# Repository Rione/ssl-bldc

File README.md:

# Ri-one BLDC Driver V1

|  | IC |
| --- | --- |
| MOSFET | [SIZ254DT-T1-GE3](https://www.mouser.jp/ProductDetail/Vishay-Siliconix/SIZ254DT-T1-GE3?qs=pUKx8fyJudCKVjpWQE2G2A%3D%3D) |
| MCU | [STM32F446RET6](https://jp.rs-online.com/web/p/microcontrollers/1106621) |
| Gate Driver | [DVR8300DRGER](https://www.ti.com/product/DRV8300/part-details/DRV8300DRGER) |
| CAN Transceiver | [TJA1441AT](https://akizukidenshi.com/catalog/g/gI-17464/) |
| Shunt Resistor| 10mΩ | 
| 3.3V Regulator | [AP7333-33SAG](https://akizukidenshi.com/catalog/g/gI-11360/) |
| Motor | [EC 45 flat 30W](https://www.maxongroup.com/medias/sys_master/root/8846629470238/20-JP-285.pdf)|

---

初めて作ったモータドライバ基板です．
記事も書いたので，良かったら見てください．
[tomixrm 初のモタドラ設計！！ゲート抵抗を計算して求めてみた](https://tomixrm.vercel.app/2e7cb67096e143f2a43334a63c00d47e)

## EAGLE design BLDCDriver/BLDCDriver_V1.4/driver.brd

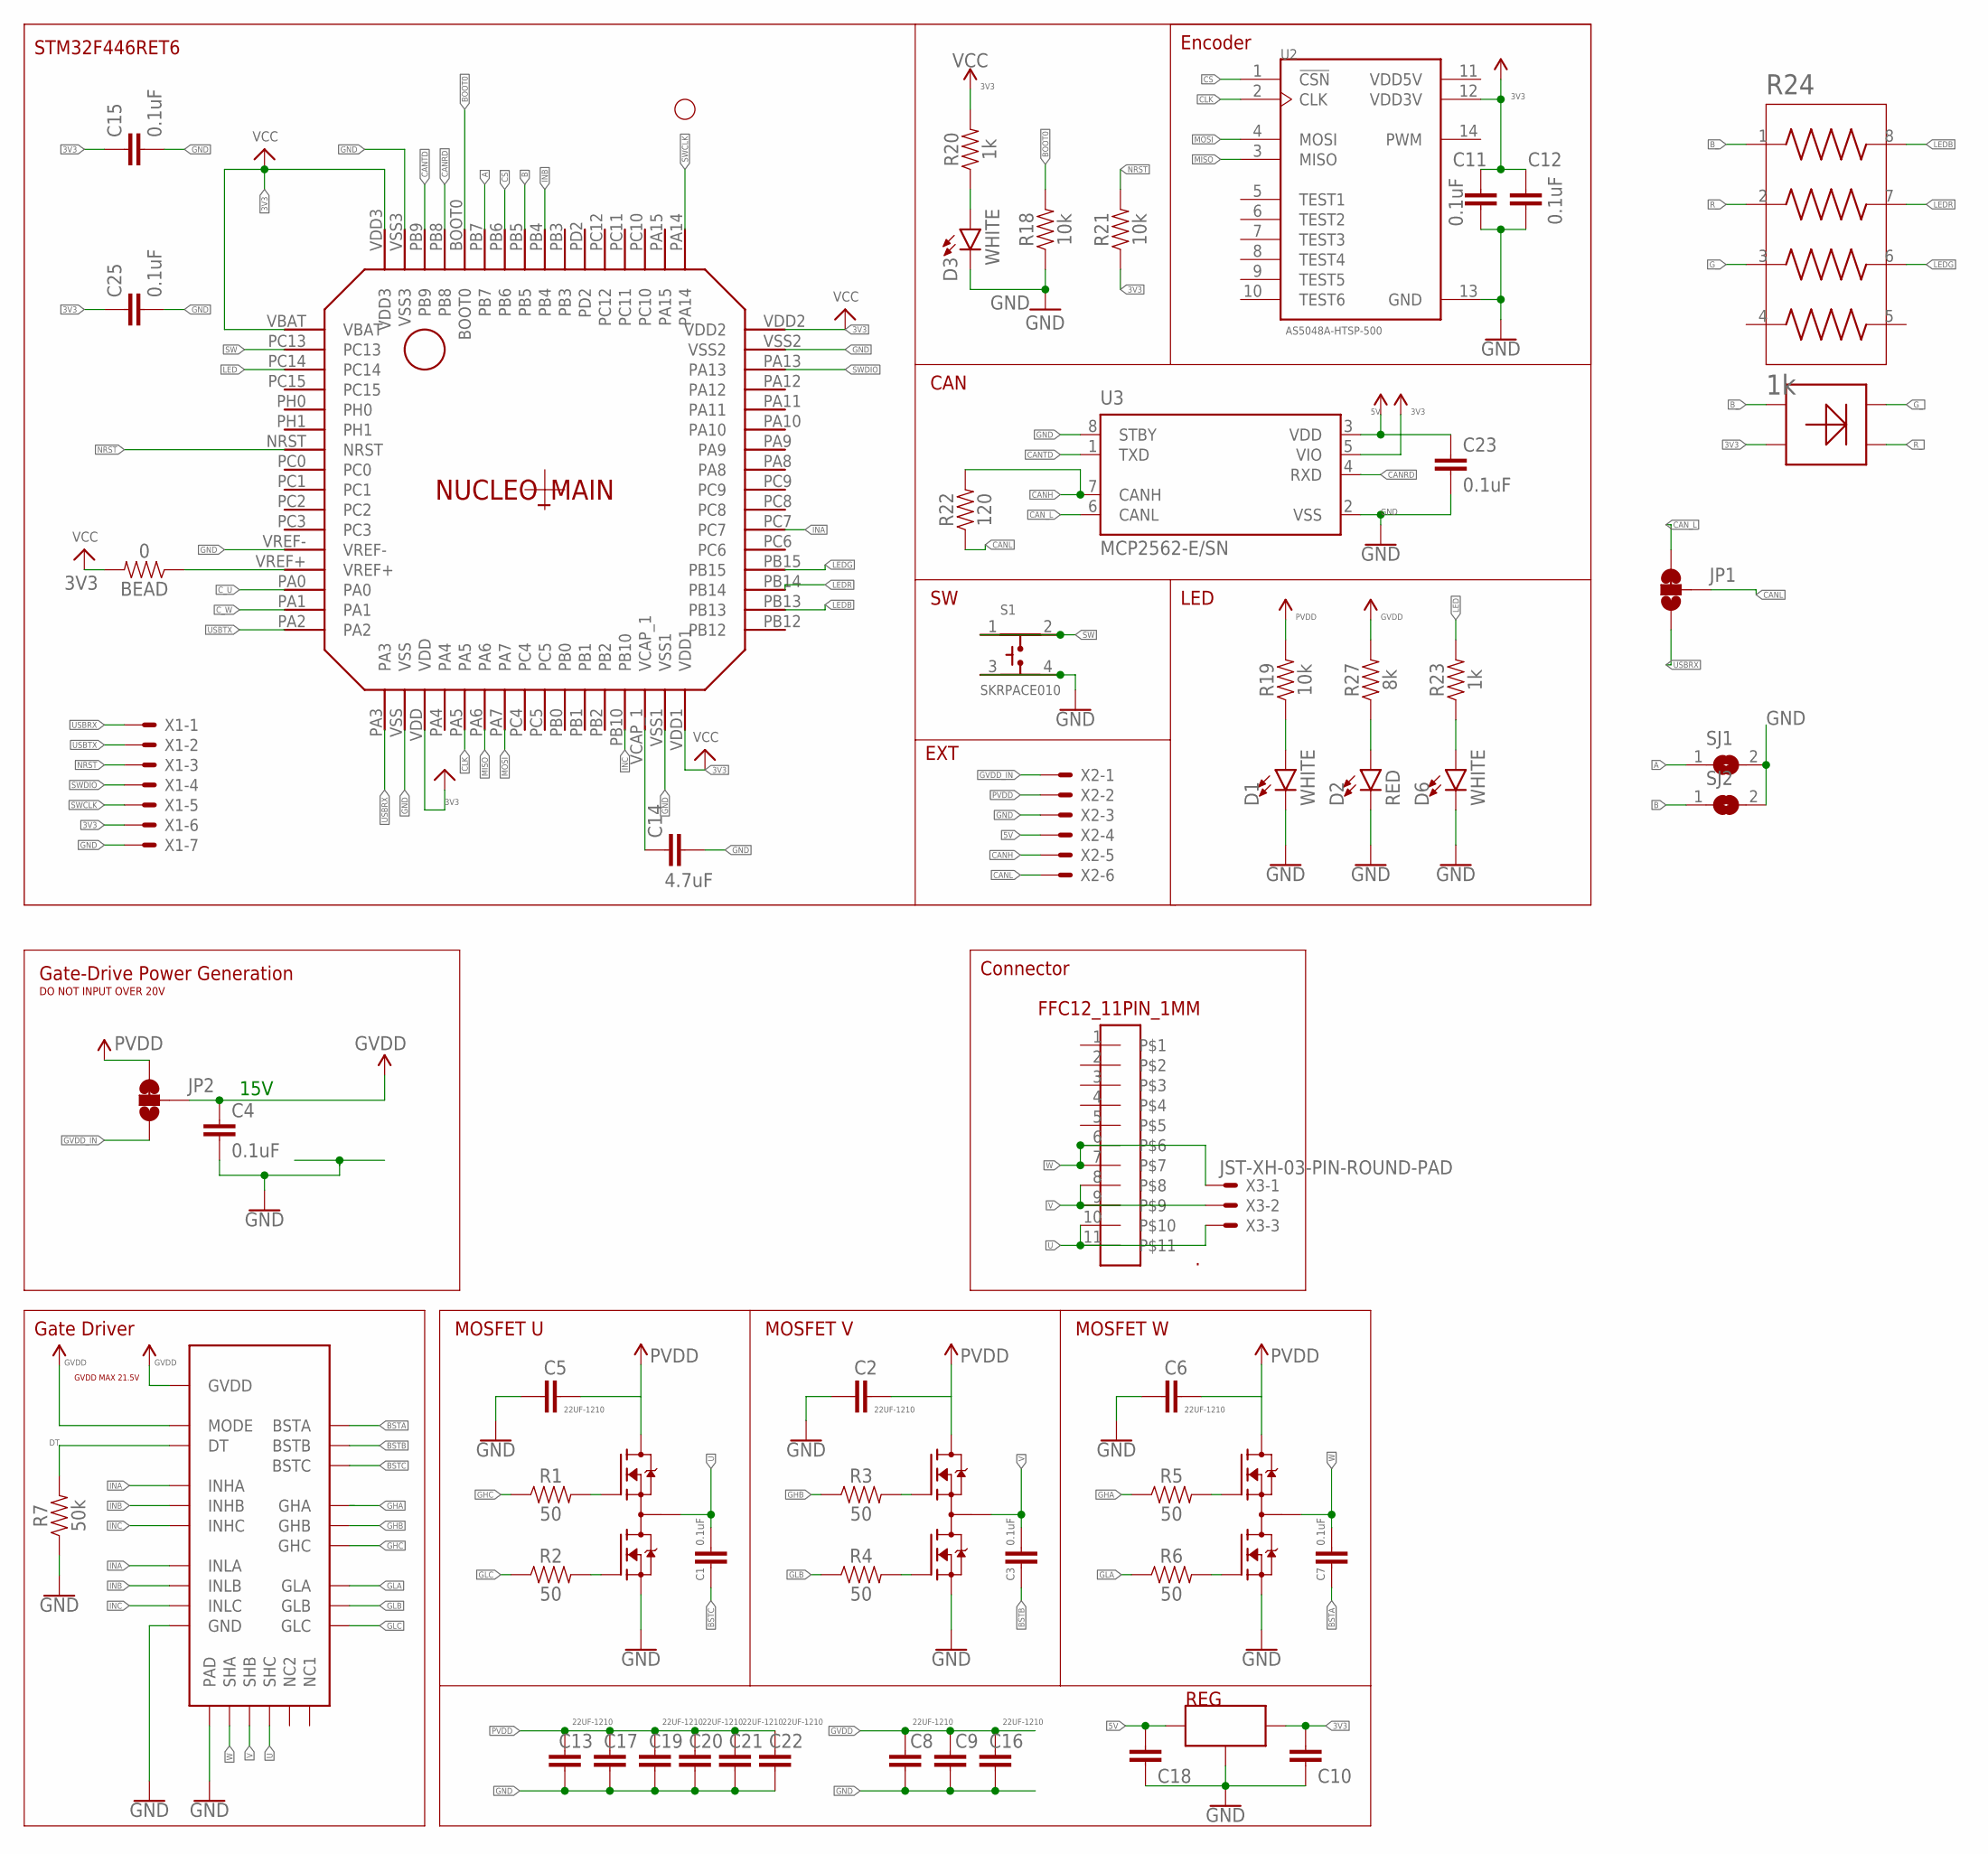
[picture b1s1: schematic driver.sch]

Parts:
.: FFC12_11PIN_1MM; CON-SMT-FFCFPC_52207-1185
BEAD: 0; 0603
C1, C3, C4, C7, C11, C12, C15, C23, C25: 0.1uF; 0603
C2, C5, C6, C8, C9, C13, C16, C17, C19, C20, C21, C22: 22UF-1210; 1210
C10, C18: 0.1UF; 1608
C14: 4.7uF; 0603
D1, D3, D6: WHITE; LED-0603
D2: RED; LED-0603
JP1, JP2: JUMPER-SMT_3_1-NC_TRACE_SILK; SMT-JUMPER_3_1-NC_TRACE_SILK
NUCLEO_MAIN: F446RET6; STM32F446RET6
Q2, Q3, Q4: SIZ240DT-T1-GE3; TRANS_SIZ240DT-T1-GE3
R1, R2, R3, R4, R5, R6: 50; 0603
R7: 50k; 0603
R18, R21: 10k; R0603
R19: 10k; 0603
R20: 1k; R0603
R22: 120; 0603
R23: 1k; 0603
R24: 1k; RESCAXS50P200X100X45-8N
R27: 8k; 0603
REG: AP7333; SOT95P237X112-3N
S1: SKRPACE010; SW_SKRPACE010
SJ1, SJ2: SJ
U1: QFN50P400X400X100-25NDRV8300DRGER; QFN50P400X400X100-25N
U2: AS5048A-HTSP-500; SOP65P640X120-14N
U3: MCP2562-E/SN; SOIC127P600X175-8N
U$1: LED; LED_AAA3528LSEKJ3ZGKQBKS
X1: JST-XH-07-PIN-ROUND-PAD; JST-XH-07-PACKAGE-ROUND-PAD
X2: JST-XH-06-PIN-LONG-PAD; JST-XH-06-PACKAGE-LONG-PAD
X3: JST-XH-03-PIN-ROUND-PAD; JST-XH-03-PACKAGE-ROUND-PAD

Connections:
3V3: BEAD.2, C10.1, C11.1, C12.1, C15.1, C25.1, NUCLEO_MAIN.VBAT, NUCLEO_MAIN.VDD, NUCLEO_MAIN.VDD1, NUCLEO_MAIN.VDD2, NUCLEO_MAIN.VDD3, R20.2, R21.1, REG.2 (OUT), U2.12 (VDD3V), U3.5 (VIO), U$1.4 (GND), X1.6
5V: C18.1, C23.1, REG.1 (IN), U3.3 (VDD), X2.4
A: NUCLEO_MAIN.PB7, SJ1.1
B: NUCLEO_MAIN.PB5, SJ2.1
BOOT0: NUCLEO_MAIN.BOOT0, R18.2
BSTA: C7.1, U1.BSTA
BSTB: C3.1, U1.BSTB
BSTC: C1.1, U1.BSTC
B_: R24.1, U$1.1 (B)
CANH: R22.2, U3.7 (CANH), X2.5
CANL: JP1.2, R22.1, X2.6
CANRD: NUCLEO_MAIN.PB8, U3.4 (RXD)
CANTD: NUCLEO_MAIN.PB9, U3.1 (TXD)
CAN_L: JP1.3, U3.6 (CANL)
CLK: NUCLEO_MAIN.PA5, U2.2 (CLK)
CS: NUCLEO_MAIN.PB6, U2.1 (!CSN)
C_U: NUCLEO_MAIN.PA0
C_W: NUCLEO_MAIN.PA1
DT: R7.2, U1.DT
GHA: R5.1, U1.GHA
GHB: R3.1, U1.GHB
GHC: R1.1, U1.GHC
GLA: R6.1, U1.GLA
GLB: R4.1, U1.GLB
GLC: R2.1, U1.GLC
GND: C2.1, C4.2, C5.1, C6.1, C8.1, C9.1, C10.2, C11.2, C12.2, C13.1, C14.2, C15.2, C16.1, C17.1, C18.2, C19.1, C20.1, C21.1, C22.1, C23.2, C25.2, D1.C, D2.C, D3.C, D6.C, NUCLEO_MAIN.VREF-, NUCLEO_MAIN.VSS, NUCLEO_MAIN.VSS1, NUCLEO_MAIN.VSS2, NUCLEO_MAIN.VSS3, Q2.5 (S2), Q2.6 (S2), Q2.7 (S2), Q3.5 (S2), Q3.6 (S2), Q3.7 (S2), Q4.5 (S2), Q4.6 (S2), Q4.7 (S2), R7.1, R18.1, REG.3 (GND), S1.3, S1.4, SJ1.2, SJ2.2, U1.GND, U1.PAD, U2.13 (GND), U3.2 (VSS), U3.8 (STBY), X1.7, X2.3
GVDD: C4.1, C8.2, C9.2, C16.2, JP2.2, R27.2, U1.GVDD, U1.MODE
GVDD_IN: JP2.1, X2.1
G_: R24.3, U$1.2 (G)
HA: Q4.1 (G1), R5.2
HB: Q3.1 (G1), R3.2
HC: Q2.1 (G1), R1.2
INA: NUCLEO_MAIN.PC7, U1.INHA, U1.INLA
INB: NUCLEO_MAIN.PB4, U1.INHB, U1.INLB
INC: NUCLEO_MAIN.PB10, U1.INHC, U1.INLC
L: D3.A, R20.1
LA: Q4.8 (G2), R6.2
LB: Q3.8 (G2), R4.2
LC: Q2.8 (G2), R2.2
LED: NUCLEO_MAIN.PC14, R23.2
LEDB: NUCLEO_MAIN.PB13, R24.8
LEDG: NUCLEO_MAIN.PB15, R24.6
LEDR: NUCLEO_MAIN.PB14, R24.7
MISO: NUCLEO_MAIN.PA6, U2.3 (MISO)
MOSI: NUCLEO_MAIN.PA7, U2.4 (MOSI)
unnamed: D1.A, R19.1
unnamed: D2.A, R27.1
unnamed: D6.A, R23.1
NRST: NUCLEO_MAIN.NRST, R21.2, X1.3
PVDD: C2.2, C5.2, C6.2, C13.2, C17.2, C19.2, C20.2, C21.2, C22.2, JP2.3, Q2.2 (D1), Q2.3 (D1), Q2.4 (D1), Q2.10 (D1), Q3.2 (D1), Q3.3 (D1), Q3.4 (D1), Q3.10 (D1), Q4.2 (D1), Q4.3 (D1), Q4.4 (D1), Q4.10 (D1), R19.2, X2.2
R_: R24.2, U$1.3 (R)
SW: NUCLEO_MAIN.PC13, S1.1, S1.2
SWCLK: NUCLEO_MAIN.PA14, X1.5
SWDIO: NUCLEO_MAIN.PA13, X1.4
U: ..10, ..11, C1.2, Q2.9 (S1/D2), U1.SHC, X3.3
USBRX: JP1.1, NUCLEO_MAIN.PA3, X1.1
USBTX: NUCLEO_MAIN.PA2, X1.2
V: ..8, ..9, C3.2, Q3.9 (S1/D2), U1.SHB, X3.2
VCAP: C14.1, NUCLEO_MAIN.VCAP_1
VDD5V: U2.11 (VDD5V)
VDDA: BEAD.1, NUCLEO_MAIN.VREF+
W: ..6, ..7, C7.2, Q4.9 (S1/D2), U1.SHA, X3.1

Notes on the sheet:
GVDD MAX 21.5V
15V
Gate-Drive Power Generation
Gate Driver
MOSFET U
Connector
Encoder
STM32F446RET6
MOSFET V
MOSFET W
DO NOT INPUT OVER 20V
CAN
LED
EXT

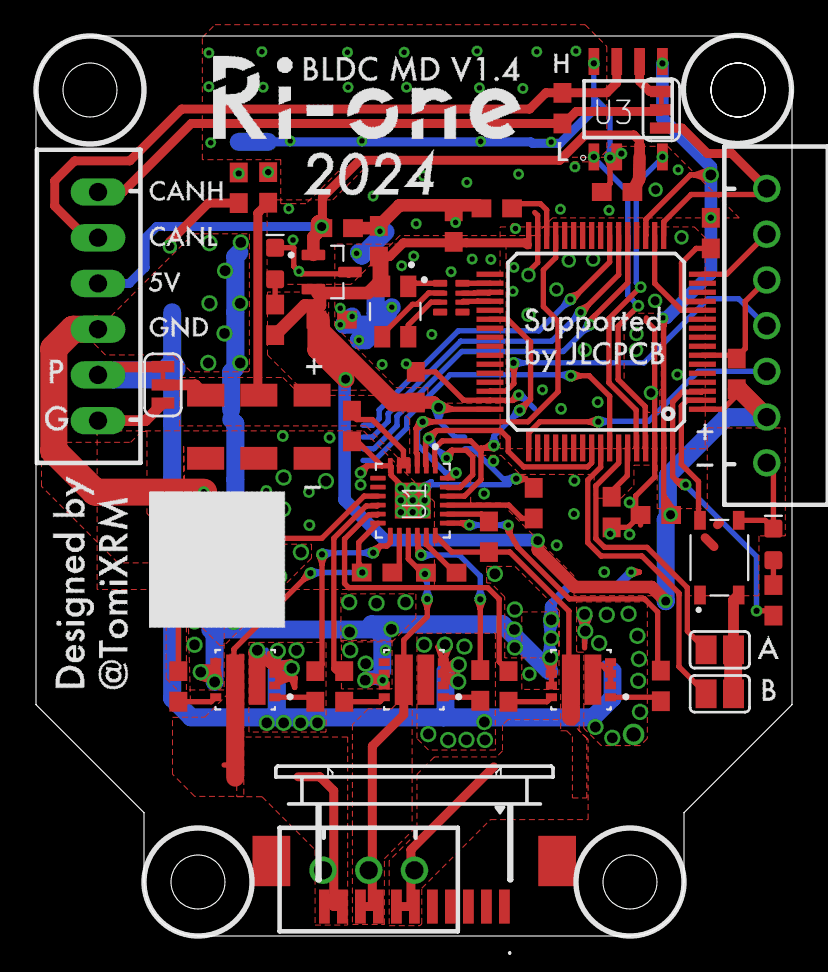
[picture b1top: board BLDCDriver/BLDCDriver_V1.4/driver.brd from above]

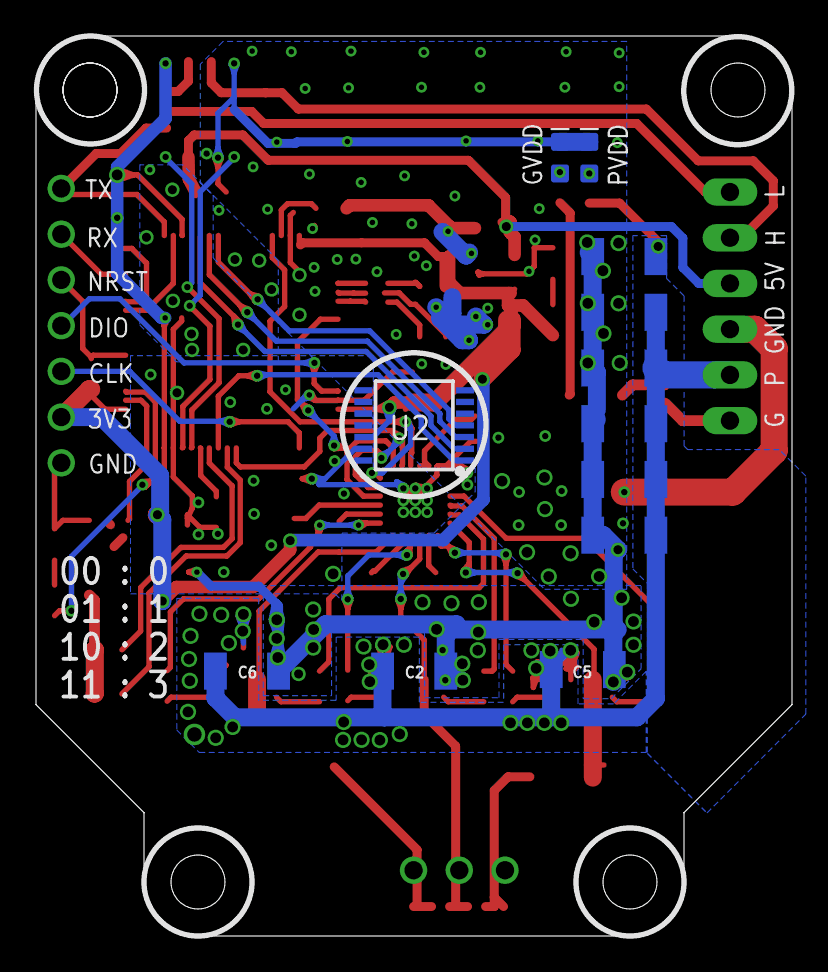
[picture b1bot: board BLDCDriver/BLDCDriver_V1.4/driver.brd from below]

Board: 2 copper layers, 42.0 x 50.0 mm, 62 parts (12 on the bottom side), 59 nets.

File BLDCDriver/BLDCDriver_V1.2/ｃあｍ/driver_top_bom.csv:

Comment,Designator,Footprint,LCSC Part #
BLM18EG601SN1D,BEAD,603,
0.1uF,C10 C18,603,
0.1uF,C1 C3 C4 C7 C11 C12 C15 C23,603,
1k,R20,603,
1k,R23,603,
4.7uF,C14,603,
10k,R27,603,
10k,R18,603,
10k,R19,603,
10k,R21,603,
22UF-1210,C8 C9 C16 C24,1210,
0603WAJ0510T5E,R1 R2 R3 R4 R5 R6,603,HP03W5F500JT5E
50k,R7,603,
AP7333-33SRG-7,REG,SOT95P237X112-3N,
F446RET6,NUCLEO_MAIN,STM32F446RET6,
FFC12_11PIN_1MM,.,CON-SMT-FFCFPC_52207-1185,
JUMPER-SMT_3_1-NC_TRACE_SILK,JP2,SMT-JUMPER_3_1-NC_TRACE_SILK,
MCP2562-E/SN,U3,SOIC127P600X175-8N,
DRV8300DRGER,U1,QFN50P400X400X100-25N,
SIZ240DT-T1-GE3,Q2 Q3 Q4,TRANS_SIZ240DT-T1-GE3,
SKRPACE010,S1,SW_SKRPACE010,
WHITE,D3 D6,LED-0603,

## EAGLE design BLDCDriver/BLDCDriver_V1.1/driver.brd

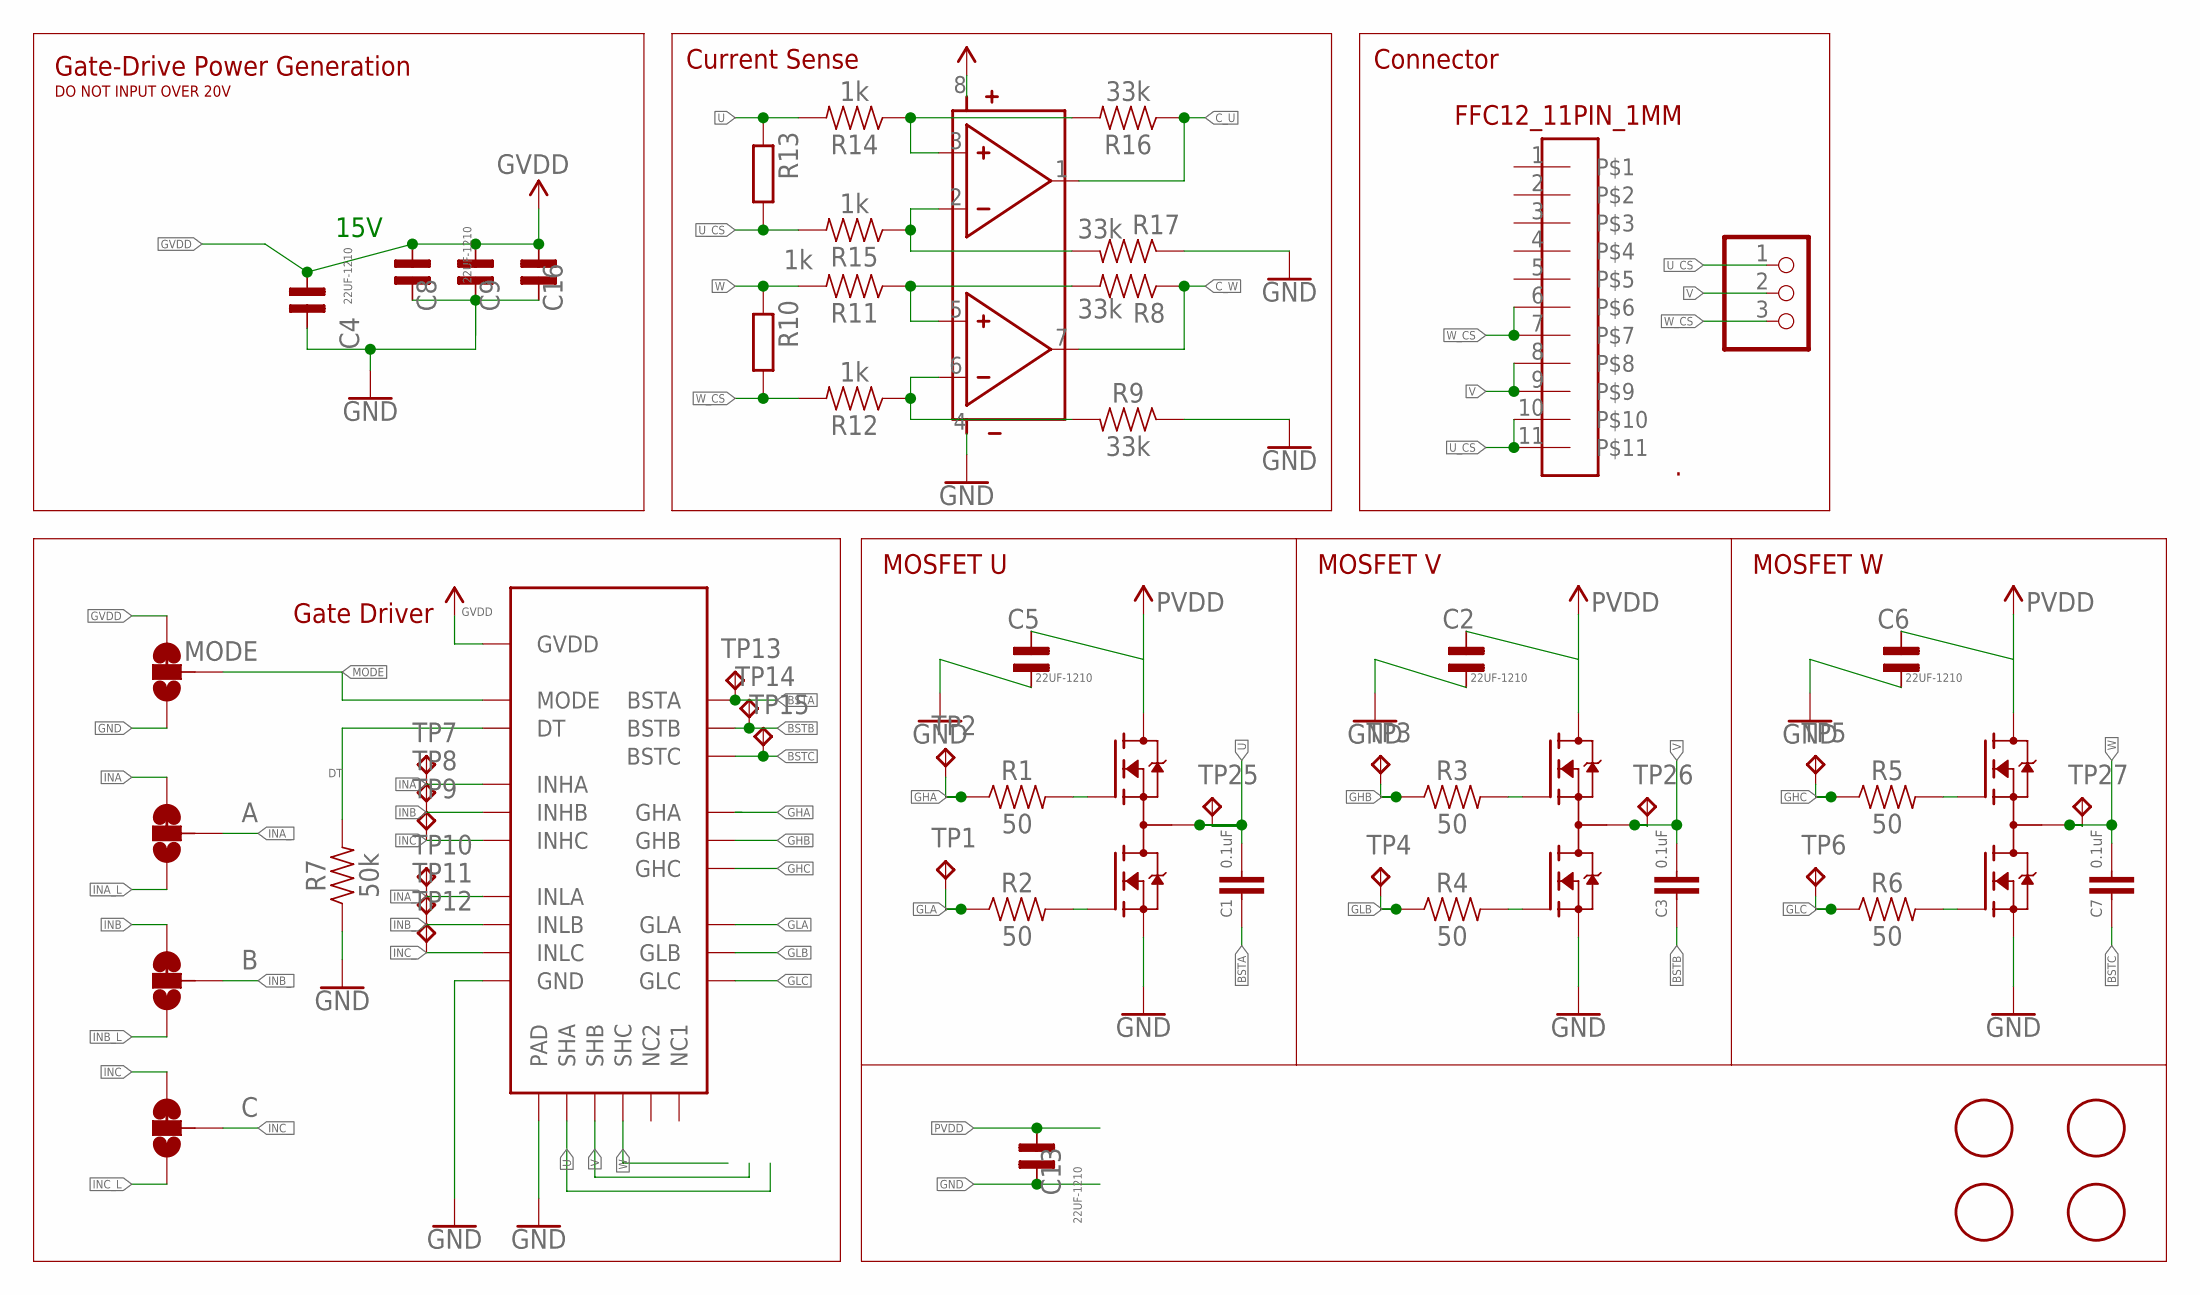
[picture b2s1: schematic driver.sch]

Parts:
.: FFC12_11PIN_1MM; CON-SMT-FFCFPC_52207-1185
A: JUMPER-SMT_3_1-NC_TRACE_SILK; SMT-JUMPER_3_1-NC_TRACE_SILK
B: JUMPER-SMT_3_1-NC_TRACE_SILK; SMT-JUMPER_3_1-NC_TRACE_SILK
C: JUMPER-SMT_3_1-NC_TRACE_SILK; SMT-JUMPER_3_1-NC_TRACE_SILK
C1, C3, C7: 0.1uF; 0603
C2, C5, C6, C8, C9, C13, C16: 22UF-1210; 0805
C4: 0.1uF; 0805
JP3: PINHD-1X3CB; 1X03-CLEANBIG
MODE: JUMPER-SMT_3_1-NC_TRACE_SILK; SMT-JUMPER_3_1-NC_TRACE_SILK
Q2, Q3, Q4: SIZ240DT-T1-GE3; TRANS_SIZ240DT-T1-GE3
R1, R2, R3, R4, R5, R6: 50; 0603
R7: 50k; 0603
R8, R9, R16, R17: 33k; 0603
R10, R13: SMS-REF
R11, R12, R14, R15: 1k; 0603
TP1, TP2, TP3, TP4, TP5, TP6, TP7, TP8, TP9, TP10, TP11, TP12, TP13, TP14, TP15, TP25, TP26, TP27: TPPAD1-13; P1-13
U1: QFN50P400X400X100-25NDRV8300DRGER; QFN50P400X400X100-25N
U4: SOP80P620X125-8N
U$1, U$3, U$4, U$5: PIN; 3MM

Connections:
3V3: U4.8 (VDD)
BSTA: C1.1, TP13.TP, U1.BSTA
BSTB: C3.1, TP14.TP, U1.BSTB
BSTC: C7.1, TP15.TP, U1.BSTC
C_U: R16.1, U4.1 (O1)
C_W: R8.1, U4.7 (O2)
DT: R7.2, U1.DT
GHA: R1.1, TP2.TP, U1.GHA
GHB: R3.1, TP3.TP, U1.GHB
GHC: R5.1, TP5.TP, U1.GHC
GLA: R2.1, TP1.TP, U1.GLA
GLB: R4.1, TP4.TP, U1.GLB
GLC: R6.1, TP6.TP, U1.GLC
GND: C2.1, C4.2, C5.1, C6.1, C8.1, C9.1, C13.1, C16.1, MODE.1, Q2.5 (S2), Q2.6 (S2), Q2.7 (S2), Q3.5 (S2), Q3.6 (S2), Q3.7 (S2), Q4.5 (S2), Q4.6 (S2), Q4.7 (S2), R7.1, R9.1, R17.1, U1.GND, U1.PAD, U4.4 (GND)
GVDD: C4.1, C8.2, C9.2, C16.2, MODE.3, U1.GVDD
HA: Q2.1 (G1), R1.2
HB: Q3.1 (G1), R3.2
HC: Q4.1 (G1), R5.2
INA: A.3, TP7.TP, U1.INHA
INA_: A.2, TP10.TP, U1.INLA
INA_L: A.1
INB: B.3, TP8.TP, U1.INHB
INB_: B.2, TP11.TP, U1.INLB
INB_L: B.1
INC: C.3, TP9.TP, U1.INHC
INC_: C.2, TP12.TP, U1.INLC
INC_L: C.1
LA: Q2.8 (G2), R2.2
LB: Q3.8 (G2), R4.2
LC: Q4.8 (G2), R6.2
MODE: MODE.2, U1.MODE
unnamed: R8.2, R11.1, U4.5 (P2)
unnamed: R9.2, R12.1, U4.6 (M2)
unnamed: R14.1, R16.2, U4.3 (P1)
unnamed: R15.1, R17.2, U4.2 (M1)
PVDD: C2.2, C5.2, C6.2, C13.2, Q2.2 (D1), Q2.3 (D1), Q2.4 (D1), Q2.10 (D1), Q3.2 (D1), Q3.3 (D1), Q3.4 (D1), Q3.10 (D1), Q4.2 (D1), Q4.3 (D1), Q4.4 (D1), Q4.10 (D1)
U: C1.2, Q2.9 (S1/D2), R13.2, R14.2, TP25.TP, U1.SHA
U_CS: ..10, ..11, JP3.1, R13.1, R15.2
V: ..8, ..9, C3.2, JP3.2, Q3.9 (S1/D2), TP26.TP, U1.SHB
W: C7.2, Q4.9 (S1/D2), R10.2, R11.2, TP27.TP, U1.SHC
W_CS: ..6, ..7, JP3.3, R10.1, R12.2

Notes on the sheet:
15V
Gate-Drive Power Generation
Gate Driver
MOSFET U
Current Sense
Connector
MOSFET V
MOSFET W
DO NOT INPUT OVER 20V

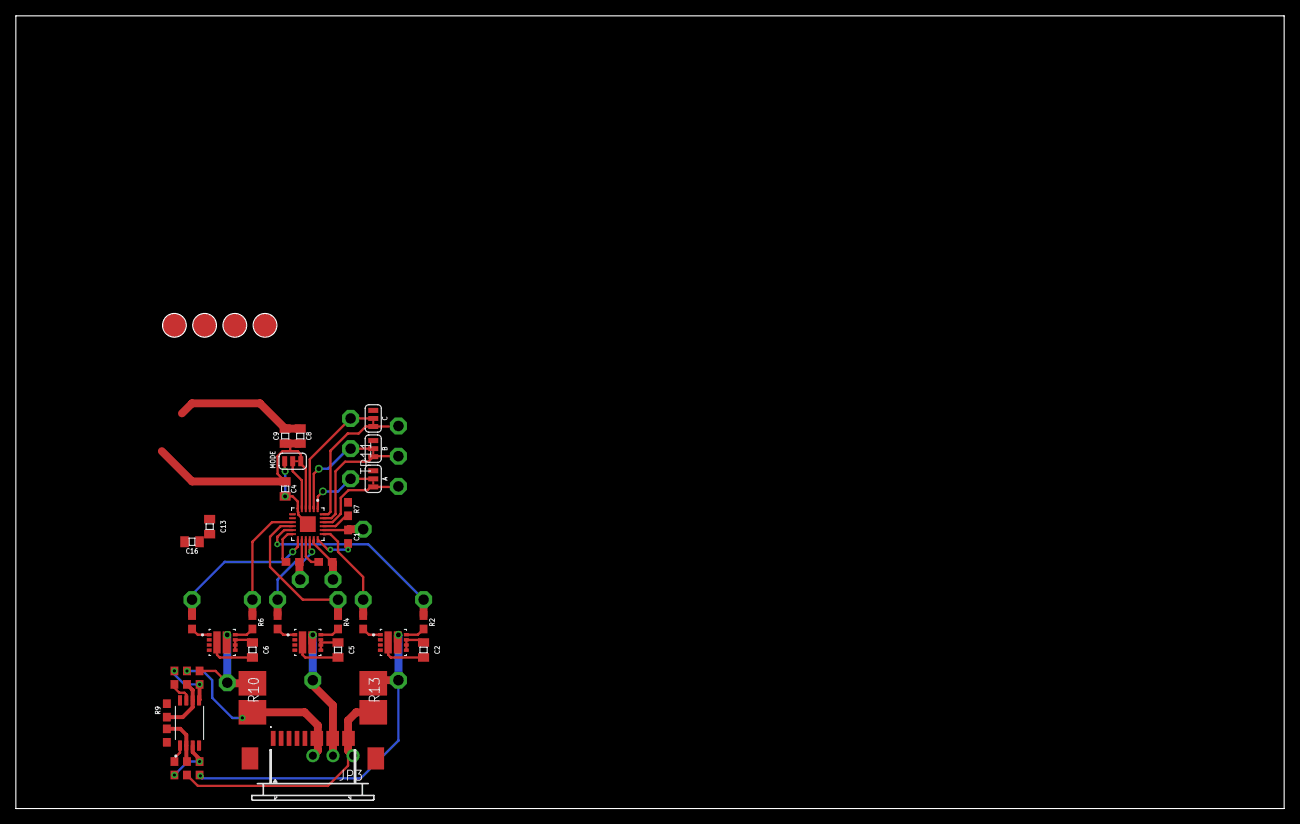
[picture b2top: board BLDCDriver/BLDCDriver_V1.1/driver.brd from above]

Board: 2 copper layers, 159.9 x 99.9 mm, 61 parts (0 on the bottom side), 37 nets.

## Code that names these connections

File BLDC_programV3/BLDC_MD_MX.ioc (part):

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Mcu.Name=STM32F446R(C-E)Tx
Mcu.Package=LQFP64
Mcu.UserName=STM32F446RETx
PA0-WKUP.GPIOParameters=GPIO_Label
PA0-WKUP.GPIO_Label=C_U
PA0-WKUP.Signal=GPIO_Analog
PA1.GPIOParameters=GPIO_Label
PA1.GPIO_Label=C_W
PA1.Signal=GPIO_Analog
PA13.Mode=Serial_Wire
PA13.Signal=SYS_JTMS-SWDIO
PA14.Mode=Serial_Wire
PA14.Signal=SYS_JTCK-SWCLK
PA2.GPIOParameters=GPIO_Label
PA2.GPIO_Label=USBTX
PA2.Mode=Asynchronous
PA2.Signal=USART2_TX
PA3.GPIOParameters=GPIO_Label
PA3.GPIO_Label=USBRX
PA3.Mode=Asynchronous
PA3.Signal=USART2_RX
PA4.Mode=NSS_Signal_Hard_Output
PA4.Signal=SPI1_NSS
PA5.Mode=Full_Duplex_Master
PA5.Signal=SPI1_SCK
PA6.Mode=Full_Duplex_Master
PA6.Signal=SPI1_MISO
PA7.Mode=Full_Duplex_Master
PA7.Signal=SPI1_MOSI
PB10.GPIOParameters=GPIO_Label
PB10.GPIO_Label=PWM_C
PB10.Signal=S_TIM2_CH3
PB13.GPIOParameters=GPIO_Label
PB13.GPIO_Label=BLUE
PB13.Signal=GPIO_Output
PB14.GPIOParameters=GPIO_Label
PB14.GPIO_Label=RED
PB14.Signal=GPIO_Output
PB15.GPIOParameters=GPIO_Label
PB15.GPIO_Label=GREEN
PB15.Signal=GPIO_Output
PB4.GPIOParameters=GPIO_Label
PB4.GPIO_Label=PWM_B
PB4.Signal=S_TIM3_CH1
PB5.GPIOParameters=GPIO_Label
PB5.GPIO_Label=IDIN_B
PB5.Signal=GPIO_Input
PB6.GPIOParameters=GPIO_Label
PB6.GPIO_Label=SPI1_CS
PB6.Signal=GPIO_Output
PB7.GPIOParameters=GPIO_Label
PB7.GPIO_Label=IDIN_A
PB7.Signal=GPIO_Input
PB8.Mode=CAN_Activate
PB8.Signal=CAN1_RX
PB9.Mode=CAN_Activate
PB9.Signal=CAN1_TX
PC13.Signal=GPIO_Input
PC14-OSC32_IN.GPIOParameters=GPIO_Label
PC14-OSC32_IN.GPIO_Label=LED
PC14-OSC32_IN.Signal=GPIO_Output
PC7.GPIOParameters=GPIO_Label
PC7.GPIO_Label=PWM_A
PC7.Signal=S_TIM3_CH2
RCC.SYSCLKFreq_VALUE=180000000
RCC.SYSCLKSource=RCC_SYSCLKSOURCE_PLLCLK
board=custom

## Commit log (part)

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2022-10-15 set limitation of velocity at 100
2022-10-15 gitignore
2022-10-15 add lib
2022-10-15 achieve to turn a motor on STM32
    lib_archive = falseをするとplatoformIOのSTM32duinoがちゃんと動いてくれる
2022-10-16 add schematic
2022-10-18 gitignore : support ignore Eagle cashfile
2022-10-18 add MOSFETs on driver schematic
2022-11-04 ゲートドライバを50Ωに決定した
    詳しくは https://www.notion.so/rionessl/MOSFET-c3f0bc53d559421c83d572cacaf1d697#0553bd1ca6b7412ab2f7f6d7e1a45fa8
2022-11-05 CurrentSenseを追加した
2022-11-05 STM32と磁気エンコーダを追加した
2022-11-05 somefix
    # ==== Emojis ====
    # ✨ :sparkles: Add new feature
    # ✅ :white_check_mark: Update existing feature (not bug)
    # ⚠️ :warning: Fix bug/error
    # 🔥 :fire: Remove files or features
    # ✏️ :pencil2: Fix typos
2022-11-06 自分、泣いていいすか
2022-11-06 救いはないんですか〜？
    # ==== Emojis ====
    # ✨ :sparkles: Add new feature
    # ✅ :white_check_mark: Update existing feature (not bug)
    # ⚠️ :warning: Fix bug/error
    # 🔥 :fire: Remove files or features
    # ✏️ :pencil2: Fix typos
2022-11-07 ちょっと頑張った
    # ==== Emojis ====
    # ✨ :sparkles: Add new feature
    # ✅ :white_check_mark: Update existing feature (not bug)
    # ⚠️ :warning: Fix bug/error
    # 🔥 :fire: Remove files or features
    # ✏️ :pencil2: Fix typos
2022-11-08 モータ固定台のシルク入れた
    # ==== Emojis ====
    # ✨ :sparkles: Add new feature
    # ✅ :white_check_mark: Update existing feature (not bug)
    # ⚠️ :warning: Fix bug/error
    # 🔥 :fire: Remove files or features
    # ✏️ :pencil2: Fix typos
2022-11-08 シャント抵抗を裏側にした。GVDD消した
    # ==== Emojis ====
    # ✨ :sparkles: Add new feature
    # ✅ :white_check_mark: Update existing feature (not bug)
    # ⚠️ :warning: Fix bug/error
    # 🔥 :fire: Remove files or features
    # ✏️ :pencil2: Fix typos
2022-11-08 気合いが足りない。
    # ✨ :sparkles: Add new feature
    # ✅ :white_check_mark: Update existing feature (not bug)
    # ⚠️ :warning: Fix bug/error
    # 🔥 :fire: Remove files or features
    # ✏️ :pencil2: Fix typos
    # 📝 :memo: Update documentation
2022-11-09 CANに対応していき
    # ==== Emojis ====
    # ✨ :sparkles: Add new feature
    # ✅ :white_check_mark: Update existing feature (not bug)
    # ⚠️ :warning: Fix bug/error
    # 🔥 :fire: Remove files or features
    # ✏️ :pencil2: Fix typos
2022-11-09 ちょっと希望が見えた
2022-11-09 希望が見えてきた
2022-11-09 𝐏𝐎𝐖𝐄𝐑した
    # ==== Emojis ====
    # ✨ :sparkles: Add new feature
    # ✅ :white_check_mark: Update existing feature (not bug)
    # ⚠️ :warning: Fix bug/error
    # 🔥 :fire: Remove files or features
    # ✏️ :pencil2: Fix typos
2022-11-09 FETにビア通した
    # ==== Emojis ====
    # ✨ :sparkles: Add new feature
    # ✅ :white_check_mark: Update existing feature (not bug)
    # ⚠️ :warning: Fix bug/error
    # 🔥 :fire: Remove files or features
    # ✏️ :pencil2: Fix typos
2022-11-09 配線1からやり直し
    # ==== Emojis ====
    # ✨ :sparkles: Add new feature
    # ✅ :white_check_mark: Update existing feature (not bug)
    # ⚠️ :warning: Fix bug/error
    # 🔥 :fire: Remove files or features
    # ✏️ :pencil2: Fix typos
2022-11-09 配置プロった
    - コンデンサを追加した。
    - 電流センシングの相をVからWに変えた
    - パワーラインから配線はじめた
2022-11-09 いい感じ🦀
    # ==== Emojis ====
    # ✨ :sparkles: Add new feature
    # ✅ :white_check_mark: Update existing feature (not bug)
    # ⚠️ :warning: Fix bug/error
    # 🔥 :fire: Remove files or features
    # ✏️ :pencil2: Fix typos
2022-11-09 ゲートドライバ周りの配線全部終わらせた
    # ==== Emojis ====
    # ✨ :sparkles: Add new feature
    # ✅ :white_check_mark: Update existing feature (not bug)
    # ⚠️ :warning: Fix bug/error
    # 🔥 :fire: Remove files or features
    # ✏️ :pencil2: Fix typos
2022-11-10 CANの配線をした
    # ==== Emojis ====
    # ✨ :sparkles: Add new feature
    # ✅ :white_check_mark: Update existing feature (not bug)
    # ⚠️ :warning: Fix bug/error
    # 🔥 :fire: Remove files or features
    # ✏️ :pencil2: Fix typos
2022-11-10 電源ラインのパワみを増やした
    # ==== Emojis ====
    # ✨ :sparkles: Add new feature
    # ✅ :white_check_mark: Update existing feature (not bug)
    # ⚠️ :warning: Fix bug/error
    # 🔥 :fire: Remove files or features
    # ✏️ :pencil2: Fix typos
2022-11-11 DXFを復元した
2022-11-11 ⚡️電源周りの配線パワみ増した
2022-11-11 CANトランシーバーの近くにコンデンサつけた
2022-11-11 ボードをパネライズした
2022-11-11 位置合せピンを追加した
2022-11-11 パネライズアゲイン
2022-11-11 部品の数値を編集
    # ==== Emojis ====
    # ✨ :sparkles: Add new feature
    # ✅ :white_check_mark: Update existing feature (not bug)
    # ⚠️ :warning: Fix bug/error
    # 🔥 :fire: Remove files or features
    # ✏️ :pencil2: Fix typos
2022-11-13 発注します
    # ==== Emojis ====
    # ✨ :sparkles: Add new feature
    # ✅ :white_check_mark: Update existing feature (not bug)
    # ⚠️ :warning: Fix bug/error
    # 🔥 :fire: Remove files or features
    # ✏️ :pencil2: Fix typos
2022-11-13 発注したガーバーデータを追加した。
    # ==== Emojis ====
    # ✨ :sparkles: Add new feature
    # ✅ :white_check_mark: Update existing feature (not bug)
    # ⚠️ :warning: Fix bug/error
    # 🔥 :fire: Remove files or features
    # ✏️ :pencil2: Fix typos
2022-11-14 ステンシルデータを追加
    # ==== Emojis ====
    # ✨ :sparkles: Add new feature
    # ✅ :white_check_mark: Update existing feature (not bug)
    # ⚠️ :warning: Fix bug/error
    # 🔥 :fire: Remove files or features
    # ✏️ :pencil2: Fix typos
2022-11-15 change README.MD
    # ==== Emojis ====
    # ✨ :sparkles: Add new feature
    # ✅ :white_check_mark: Update existing feature (not bug)
    # ⚠️ :warning: Fix bug/error
    # 🔥 :fire: Remove files or features
    # ✏️ :pencil2: Fix typos
2022-11-15 BOMの作成
    # ==== Emojis ====
    # ✨ :sparkles: Add new feature
    # ✅ :white_check_mark: Update existing feature (not bug)
    # ⚠️ :warning: Fix bug/error
    # 🔥 :fire: Remove files or features
    # ✏️ :pencil2: Fix typos
2022-11-15 ゲート抵抗選定スクリプトの書き直し
2022-11-17 some fix README.MD
    ブログ記事のリンク載せた
2022-12-04 next
    # ==== Emojis ====
    # ✨ :sparkles: Add new feature
    # ✅ :white_check_mark: Update existing feature (not bug)
    # ⚠️ :warning: Fix bug/error
    # 🔥 :fire: Remove files or features
    # ✏️ :pencil2: Fix typos
2023-01-30 評価基板のアップデート
2023-03-10 fix position BST condenser
2023-04-22 create new program
2023-04-22 create new program BLDC_programV2
2023-04-22 エンコーダ原点と角速度のコードを修正
2023-04-22 limitを設けた
2023-04-22 clean files
2023-04-23 radianを使うように変更中
2023-04-23 モータドライバの故障診断プログラムを追加
2023-04-24 radianとdegreeの三角関数を作成
2023-04-25 PIDライブラリのエラーを修復
2023-04-25 abs,sqrt,atan2をMath.hに追加
2023-04-25 setPhaseVoltageにUdを追加，Diagnoseを変更中...
2023-04-25 センサードUqコントロールの検証(Diagnoseは一旦パス)
2023-04-25 速度PI制御に成功！！
2023-04-27 getTargetVelocityを追加
2023-05-02 some fix
2023-05-03 ドレミファソラシド
2023-05-27 :sparkles: version1.2完成(基板発注)
    # ==== Emojis ====
    # ✨ :sparkles: Add new feature
    # ✅ :white_check_mark: Update existing feature (not bug)
    # ⚠️ :warning: Fix bug/error
    # 🔥 :fire: Remove files or features
    # ✏️ :pencil2: Fix typos
2023-05-28 :sparkles: add CubeMX Project
    # ==== Emojis ====
    # ✨ :sparkles: Add new feature
    # ✅ :white_check_mark: Update existing feature (not bug)
    # ⚠️ :warning: Fix bug/error
    # 🔥 :fire: Remove files or features
    # ✏️ :pencil2: Fix typos
2023-05-28 :sparkles: generate PlatformIO Project form CubeMX
    # ==== Emojis ====
    # ✨ :sparkles: Add new feature
    # ✅ :white_check_mark: Update existing feature (not bug)
    # ⚠️ :warning: Fix bug/error
    # 🔥 :fire: Remove files or features
    # ✏️ :pencil2: Fix typos
2023-05-28 メモの追加
2023-05-29 :warning: CANTXとCANRXをスワップした
    # ==== Emojis ====
    # ✨ :sparkles: Add new feature
    # ✅ :white_check_mark: Update existing feature (not bug)
    # ⚠️ :warning: Fix bug/error
    # 🔥 :fire: Remove files or features
    # ✏️ :pencil2: Fix typos
2023-06-10 WIP CubeMX
    # ==== Emojis ====
    # ✨ :sparkles: Add new feature
    # ✅ :white_check_mark: Update existing feature (not bug)
    # ⚠️ :warning: Fix bug/error
    # 🔥 :fire: Remove files or features
    # ✏️ :pencil2: Fix typos
2023-06-10 :sparkles: add RGB Led
    # ==== Emojis ====
    # ✨ :sparkles: Add new feature
    # ✅ :white_check_mark: Update existing feature (not bug)
    # ⚠️ :warning: Fix bug/error
    # 🔥 :fire: Remove files or features
    # ✏️ :pencil2: Fix typos
2023-06-13 v1.4 test
    # ==== Emojis ====
    # ✨ :sparkles: Add new feature
    # ✅ :white_check_mark: Update existing feature (not bug)
    # ⚠️ :warning: Fix bug/error
    # 🔥 :fire: Remove files or features
    # ✏️ :pencil2: Fix typos
2023-06-19 :sparkles: create V2.0 in KiCAD7
    # ==== Emojis ====
    # ✨ :sparkles: Add new feature
    # ✅ :white_check_mark: Update existing feature (not bug)
    # ⚠️ :warning: Fix bug/error
    # 🔥 :fire: Remove files or features
    # ✏️ :pencil2: Fix typos
2023-10-04 プログラム忘れたけど，途中まで
    # ==== Emojis ====
    # ✨ :sparkles: Add new feature
    # ✅ :white_check_mark: Update existing feature (not bug)
    # ⚠️ :warning: Fix bug/error
    # 🔥 :fire: Remove files or features
    # ✏️ :pencil2: Fix typos
2023-10-04 :sparkles: V1.4 JLCPCBのPCBA検証用基板の設計DONE
    # ==== Emojis ====
    # ✨ :sparkles: Add new feature
    # ✅ :white_check_mark: Update existing feature (not bug)
    # ⚠️ :warning: Fix bug/error
    # 🔥 :fire: Remove files or features
    # ✏️ :pencil2: Fix typos
2023-12-14 基板生やした
2023-12-14 おそらくこれで速度司令を受けることができるようになった(未検証)
    0. ヘッダを受信
    1. vel[0]の 1byte目を受信
    2. vel[0]の 2byte目を受信
    3. vel[1]の 1byte目を受信
    4. vel[1]の 2byte目を受信
    5. vel[2]の 1byte目を受信
2023-12-26 unionだった
2023-12-27 ✨受信プログラムを修正！！
    手動でシリアル送るとうまく行くけど、Pythonで送るやつは上手く行ってない
2024-01-05 :sparkles: 無理やりフラッシュに書き込み読み出しができることが確認取れたが電源を切るとリセットされる
    リンカスクリプトを編集していないので。プログラムメモリと衝突していないのがラッキーぐらいの感覚で、危ないのでやめたほうがいい。一応成功しており、プログラムを書き換えてもデータを保持しているので成功している。
    EEPROMが乗らないのでFLASHに磁気エンコーダの値を書き込もうとしている。1万回程度で壊れるらしいが、書き込み回数より先にMDが壊れるだろうと思っている。
2024-01-06 ✨CubeMXでプロジェクト生成して、FLASH書き込み読み出しができたのと、AS5048Aを読み取れた
    - stm32pioでPlatformIOのプロジェクトに変更している
    - HAL_SPI_TransmitReceive_DMAで0xFFFFに投げて、その次に空データ送りつけて読み込みをDMAでやっている
    - DMA、めっちゃ複雑なんかと思ったけど、CubeMXでの設定はめっちゃ簡単だった。DMAと普通のやつの違いがよくわからん。DMAを使うとリングバッファ的なやつを作れるのかな。今回そんなことしてないけど。
    - DMAで16bit送るようにしているっぽい。できているのだろう。
    - AS5048Aを12bitと勘
2024-01-08 ✨PWM出力できた
    TIM1とTIM3を使って出力できた。1つのマイコンでBLDCを2つ回せるかも。
2024-01-11 ✨SerialをDMAで受信できた
    この後memsetなどを使ってfifoを実装する。
2024-01-11 ✨Serial Wrapperを書いた
    - 受信はDMAで
    - 送信は普通の送信
2024-01-11 ✨データ送信プロトコルでちゃんと受信できた
    0. ヘッダを受信
    1. vel[0]の 1byte目を受信
    2. vel[0]の 2byte目を受信
    3. vel[1]の 1byte目を受信
    4. vel[1]の 2byte目を受信
    5. vel[2]の 1byte目を受信
2024-01-11 ✨Serial,PWM,SPIを同時に宣言しても動いた
2024-01-11 ✨今のBLDCドライバようにプログラムを描き始めた
2024-01-11 ✨GPIOピンのラッパーが動いた
2024-01-12 ✨DWTを用いた実行時間計測用Timerクラスの実装完了
2024-01-12 ✨SPIのCSピンのON/OFFを1msから10nsに変更して1ループ20KHzにできた
2024-01-13 ✨CANでデータフレーム送信できた
    https://hsdev.co.jp/stm32-can/
    hcan1.Instance = CAN1;
    hcan1.Init.Prescaler = 5;
    hcan1.Init.Mode = CAN_MODE_NORMAL;
    hcan1.Init.SyncJumpWidth = CAN_SJW_1TQ;
    hcan1.Init.TimeSeg1 = CAN_BS1_6TQ;
2024-01-13 ✨CANの受信が確認できた
2024-01-13 🔥ゴミファイルを消した
2024-01-13 ✨CANのラッパー動いた
    受信割り込みでこの関数が呼び出されるので、オーバーロードする必要あり。
    void HAL_CAN_RxFifo0MsgPendingCallback(CAN_HandleTypeDef *hcan) {
    if (can.getHcan() == &hcan1) {
    can.recv(canRecvData);
    }
    }
2024-01-13 ✏️BLDCライブラリをIncludeしてコンパイルを通るようにした。
    次が処理の実装とかかな。
2024-01-14 ✨MKS CANable2.0(slcan)を使ってPython-canで送受信できた
2024-01-15 ✨FloatのPrintfに対応したはず
2024-01-15 ✨printf floatできた
    asm(".global _printf_float");
2024-01-16 ✨STSPIN32G4で基板設計を始めた
2024-01-18 ✨基板外形の更新と3Dデータのインポートをした
2024-01-18 ✨データシートを追加
2024-01-18 ✨回路を進めたよ。あとアートワーク太くするだけ。
    CANの電源が3.3Vだと厳しい印象。
2024-01-18 ✨DRCエラーを修正した
    MOSFETとゲート抵抗が近すぎると表示されるやつに関しては無視で行くしかない。
2024-01-18 ✨パワーラインのアートワークを仕上げた
    [-] GNDビア
    [-] CAN用LDO
2024-01-18 ✨ LED、LDO、ビアをやった
2024-01-19 ✨ID切り替えパッド、GNDベタ、パターン禁止エリア設定、テストポイント
    次は抵抗値の決定などをしていきたい。
2024-01-19 ✨sot23のSTEP読み込んだ
2024-01-19 ✨UARTで受信できる保険をかけた
2024-01-19 ⚠️PB8_BOOT0をGNDに落とした
    データシート読まないと...
2024-01-20 ✨Productionファイル生成した
2024-01-21 ⚠️電源のシルク逆、SPI_CS繋がってないのを修正、GNDベタ最適化、Production
    結構気づかなかったらやばかったやつばっかり
2024-01-25 ペリフェラルテスト開始
2024-01-25 ✨printfできた
    asm(".global _printf_float");
2024-01-25 ✨内蔵Flashにデータを書き込めました！！
    https://www.tomixrm.dev/STM32G431-Flash-HAL-7a6e0c2df70440688db178d7560de847
2024-01-26 ✨CAN通信できた。
    このサイトでCANのSample PointとボーレートからPrescalerの値などを出した。
    - 1000kBit/s
    - Sample Point 85%
    この2点を注意して以下のサイトでパラメータを計算させました。
    https://phryniszak.github.io/stm32g-fdcan/
2024-02-29 ✏️LEDのRGBの配線を修正・Lチカを確認・DCDCの出力にコンデンサを追加
2024-03-01 ✨PWM出力ができていることがわかったが、プロテクションが悪さをしておりまだモータ駆動はできていない。
2024-03-01 ✨MDで強制転流できたど〜〜〜〜！！！！
    RESETレジスタが大事だったっぽい。Device STATUS registerを眺めていたらモータが回る時と回らない時があって、見たらRESETレジスタだったので、操作したら動いた。
2024-03-22 ✨フットプリントをMAX3051に変更
2024-03-26 ✨LPF,PIDのライブラリを追加
2024-03-26 ✨エンコーダで読み取ってとりあえず回すやつできた
2024-03-26 ✏️ファイル分割をした
2024-03-27 ✨CANから目標速度を送って追従するように回すことができた

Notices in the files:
parts and their libraries:
SparkFun-Jumpers: Licensing: Creative Commons ShareAlike 4.0 International - https://creativecommons.org/licenses/by-sa/4.0
